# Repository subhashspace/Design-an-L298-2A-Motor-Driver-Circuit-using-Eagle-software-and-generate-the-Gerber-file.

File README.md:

# Design-an-L298-2A-Motor-Driver-Circuit-using-Eagle-software-and-generate-the-Gerber-file.
### Exp 8: Design an L298 2A Motor Driver Circuit using Eagle software and generate the Gerber file.

# AIM:
To design the schematic and PCB layout diagram of an L298 2A Motor Driver Circuit using Eagle software.
# EQUIPMENT REQUIRED:
●	Hardware: Personal Computer (PC)<br>
●	Software: Eagle <br>
# PROCEDURE:
	Create a New Project:<br>
o	Launch EAGLE and start a new project for your PCB design.<br>
o	Within the project, create a new schematic file.<br>
	Add Components:<br>
o	Utilize the built-in libraries in EAGLE or create custom libraries if needed.<br>
o	Use the 'Add' tool to place the required components onto the schematic sheet.<br>
	Make Connections:<br>
o	Connect the components using the 'Net' tool.<br>
o	Label the nets clearly to maintain clarity and organization in your design.<br>
	Check for Errors:<br>
o	Once the schematic design is complete, perform an Electrical Rule Check (ERC) to identify and correct any errors.<br>
o	Save the schematic after confirming that no errors are present.<br>
	Switch to Board Layout:<br>
o	Click on the 'Generate/Switch to Board' button to create the PCB layout from the schematic.<br>
	Arrange Components and Route Traces:<br>
o	In the board layout editor, arrange the components to optimize space and reduce signal interference.<br>
o	Use the 'Route' tool to connect the components based on the schematic design.<br>
o	Ensure proper routing by utilizing the available editing tools in EAGLE to avoid design rule violations.<br>
	Design Rule Check (DRC):<br>
o	Perform a Design Rule Check (DRC) to ensure that the routing and layout comply with design standards and that there are no issues.<br>
o	Save the board layout after resolving any errors.<br>
	Generate Gerber Files:<br>
o	Go to File > CAM Processor and configure the CAM jobs to generate Gerber files for all PCB layers, such as copper layers, silkscreen, solder mask, and drill files.<br>
o	Verify the generated files to ensure they contain all necessary information for manufacturing.<br>
	Save Manufacturing Files:<br>
o	Save the Gerber files and any other required manufacturing files to send to your PCB manufacturer for fabrication.<br>
# THEORY:
The L298 is a dual H-Bridge motor driver IC that allows you to control two DC motors or a single stepper motor. It can drive motors with voltage up to 46V and current up to 2A per channel, hence it's suitable for medium-power applications.
### Key features of the L298:
•	Dual full-bridge drivers (can control two motors independently)<br>
•	TTL logic compatible inputs<br>
•	Separate power supply for logic and motor<br>
•	Built-in diodes for back EMF protection<br>
•	Enable pins for PWM-based speed control<br>
In the given circuit:
•	U1 is the L298 IC<br>
•	U2 is a 7805 voltage regulator used to step down 12V to 5V for logic<br>
•	C1 and C2 are electrolytic capacitors for filtering<br>
•	D1 is an LED with resistor R1 for power indication<br>
### Working of the Circuit
1.	Power Supply:<br>
o	A 12V power source is connected to the circuit.<br>
o	The 7805 voltage regulator (U2) steps this down to 5V for logic components.<br>
o	The 5V output also powers the logic (VS) pin of the L298, while the motor power (VCC) pin is fed with 12V.<br>
2.	Input Control:<br>
o	Inputs IN1–IN4 are connected to a microcontroller or control logic, which sends signals to determine motor direction.<br>
o	ENA and ENB are enable pins, used for speed control via PWM.<br>
3.	Motor Outputs:<br>
o	OUT1–OUT4 are connected to the terminals of two motors.<br>
o	Depending on the input combinations (HIGH/LOW), the motors can rotate forward, backward, or stop.<br>
4.	Diode Protection:<br>
o	The diodes connected across the motor output pins are for flyback protection. They absorb voltage spikes due to back EMF generated by the motors when switching.<br>
5.	Operation Example:<br>
o	If IN1 = HIGH and IN2 = LOW, motor 1 rotates in one direction.<br>
o	Reversing the logic (IN1 = LOW, IN2 = HIGH) makes it rotate in the opposite direction.<br>
o	When both inputs are the same, the motor stops.<br>

# CIRCUIT DIAGRAM:

# EXPECTED OUTPUT:
### Schematic diagram

### Layout diagram

# RESULT:
Thus, the schematic and PCB layout for the L298 2A Motor Driver Circuit has been successfully designed using Eagle software.

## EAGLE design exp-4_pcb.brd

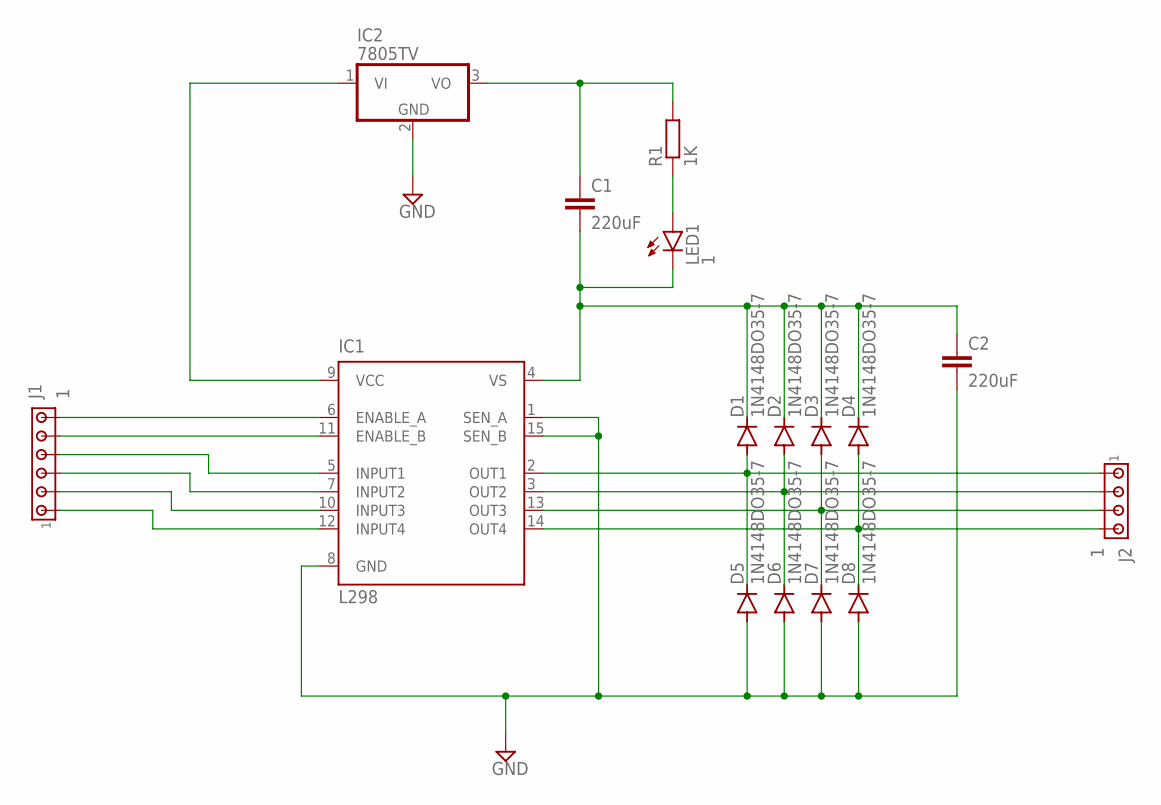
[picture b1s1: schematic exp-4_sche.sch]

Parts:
C1, C2: 220uF; C2.5-3
D1, D2, D3, D4, D5, D6, D7, D8: 1N4148DO35-7; DO35-7
IC1: L298; MULTIWATT-15
IC2: 7805TV; TO220V
J1: 1; 1X6MTA
J2: 1; 1X4MTA
LED1: 1; LED5MM
R1: 1K; 0204/7

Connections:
GND: C2.2, D5.A, D6.A, D7.A, D8.A, IC1.1 (SEN_A), IC1.8 (GND), IC1.15 (SEN_B), IC2.2 (GND)
unnamed: IC1.9 (VCC), IC2.1 (VI)
unnamed: C1.1, IC2.3 (VO), R1.2
unnamed: C1.2, C2.1, D1.C, D2.C, D3.C, D4.C, IC1.4 (VS), LED1.K (C)
unnamed: LED1.A, R1.1
unnamed: D1.A, D5.C, IC1.2 (OUT1), J2.1
unnamed: IC1.6 (ENABLE_A), J1.6
unnamed: IC1.11 (ENABLE_B), J1.5
unnamed: IC1.5 (INPUT1), J1.4
unnamed: IC1.7 (INPUT2), J1.3
unnamed: IC1.10 (INPUT3), J1.2
unnamed: IC1.12 (INPUT4), J1.1
unnamed: D2.A, D6.C, IC1.3 (OUT2), J2.2
unnamed: D3.A, D7.C, IC1.13 (OUT3), J2.3
unnamed: D4.A, D8.C, IC1.14 (OUT4), J2.4

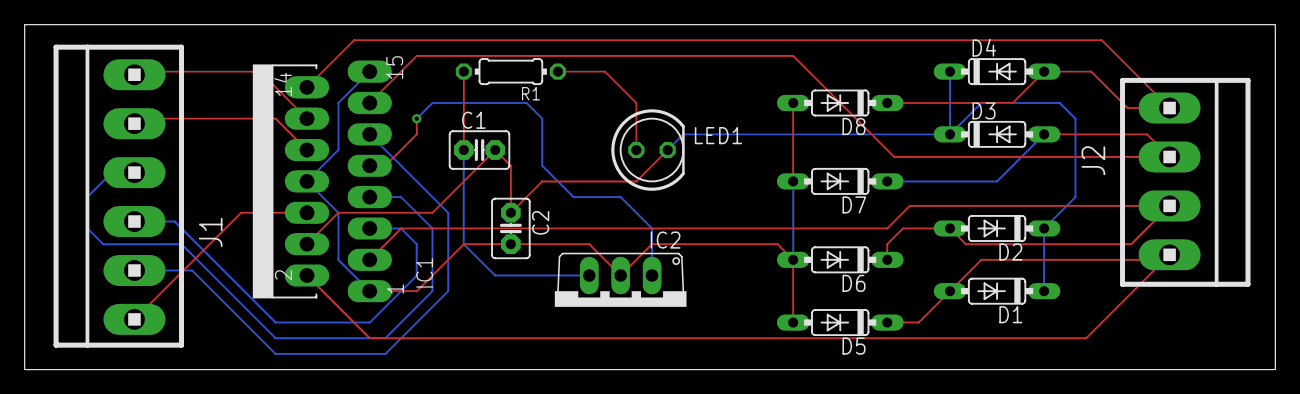
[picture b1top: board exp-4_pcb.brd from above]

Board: 2 copper layers, 101.3 x 27.9 mm, 16 parts (0 on the bottom side), 15 nets.
